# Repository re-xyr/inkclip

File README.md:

# Inkclip

Inkclip is an e-paper hair clip.

## Features

- It looks cool, if you are the type of person who thinks this kind of things look cool.
- Use it as more than a hair clip: a pin, a pocket clip, or just a gadget on your desktop.
- Update the pattern on the hair clip by simply connecting it to a computer via USB.
  - There is a ready-made web application you can use for this!
- Everything is open source: the hardware, the firmware, and the webapp.

## Physical characteristics

- Display size: 1.54 inches
- Resolution: 200 x 200 px
- Color: black and white
- Thickness (average): 2.60mm
- Thickness (thickest): 5.00mm (at micro-B port)
- Minimum weight (without mounting hardware): 6.5g
- Typical weight (with a 35mm hair clip): 8.0g
- Size: 33.40mm x 33.92mm
  - The shape of the device is a 32.80mm x 38.32mm rectangle with 1mm-radius dogbone corners.

## Project structure

- `hardware/` is the KiCad project for the Inkclip hardware.
- `firmware/` is a simple firmware for Inkclip that receives image bitmaps and then updates the entire display.
- `webapp/` is a web application for updating the display that works with the aforementioned firmware.

## Demo

## License

The hardware design portion of this project is available under the *CERN Open Hardware Licence Version 2 - Strongly Reciprocal (`CERN-OHL-S-2.0`)* while the software portion is available under the *GNU General Public License v3.0 or later (`GPL-3.0-or-later`)*. For details, refer to the `LICENSE` files under each subdirectory of this repository.

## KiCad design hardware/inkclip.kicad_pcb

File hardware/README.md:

# PCB design files of Inkclip

This is the [KiCad](https://www.kicad.org/) project for the PCB design of Inkclip. This PCB is designed to work with [Waveshare's 1.54-inch e-paper](https://www.waveshare.com/product/1.54inch-e-paper.htm).

The shape of the PCB is a 32.80 x 38.32mm rectangle with 1mm-radius dogbone corners. This ensures 0.5mm clearance from the PCB edge to the e-paper everywhere along the edges. Approximately in the middle of the PCB there is a 7.5mm wide horizontal component-free zone where you may attach mounting solutions of your choice (e.g. a hairclip, a pin, a pocket clip, velcro, tape, etc).

Specifically notice that the 24-pin FPC connector must be *top-contact* since the FPC cable of the display module is supposed to bend over so that the display may be mounted on the back side of the PCB. The positioning of this FPC connector is under the assumption that the PCB is 1.0mm thick, which is the thinnest [JLCPCB](https://jlcpcb.com) could print without the price going up. If you plan to print a thinner/thicker PCB then you might need to adjust the position of this connector accordingly.

This design uses an [STM32F411CEU6](https://www.st.com/en/microcontrollers-microprocessors/stm32f411ce.html) MCU. It has 512kB flash and 128kB RAM, which should be significantly more than what is needed by the firmware provided in this repository. On the bottom-right corner of the PCB there are pin holes for SWD debugging in the order [GND, SWCLK, SWDIO, 3V3]. The pushbutton on the PCB pulls BOOT0 up, which brings the MCU into DFU mode where you can write firmware over USB.

## License

The hardware design of Inkclip, namely all files under this directory, is provided under [CERN Open Hardware License Version 2 - Strongly Reciprocal (`CERN-OHL-S-2.0`)](LICENSE).

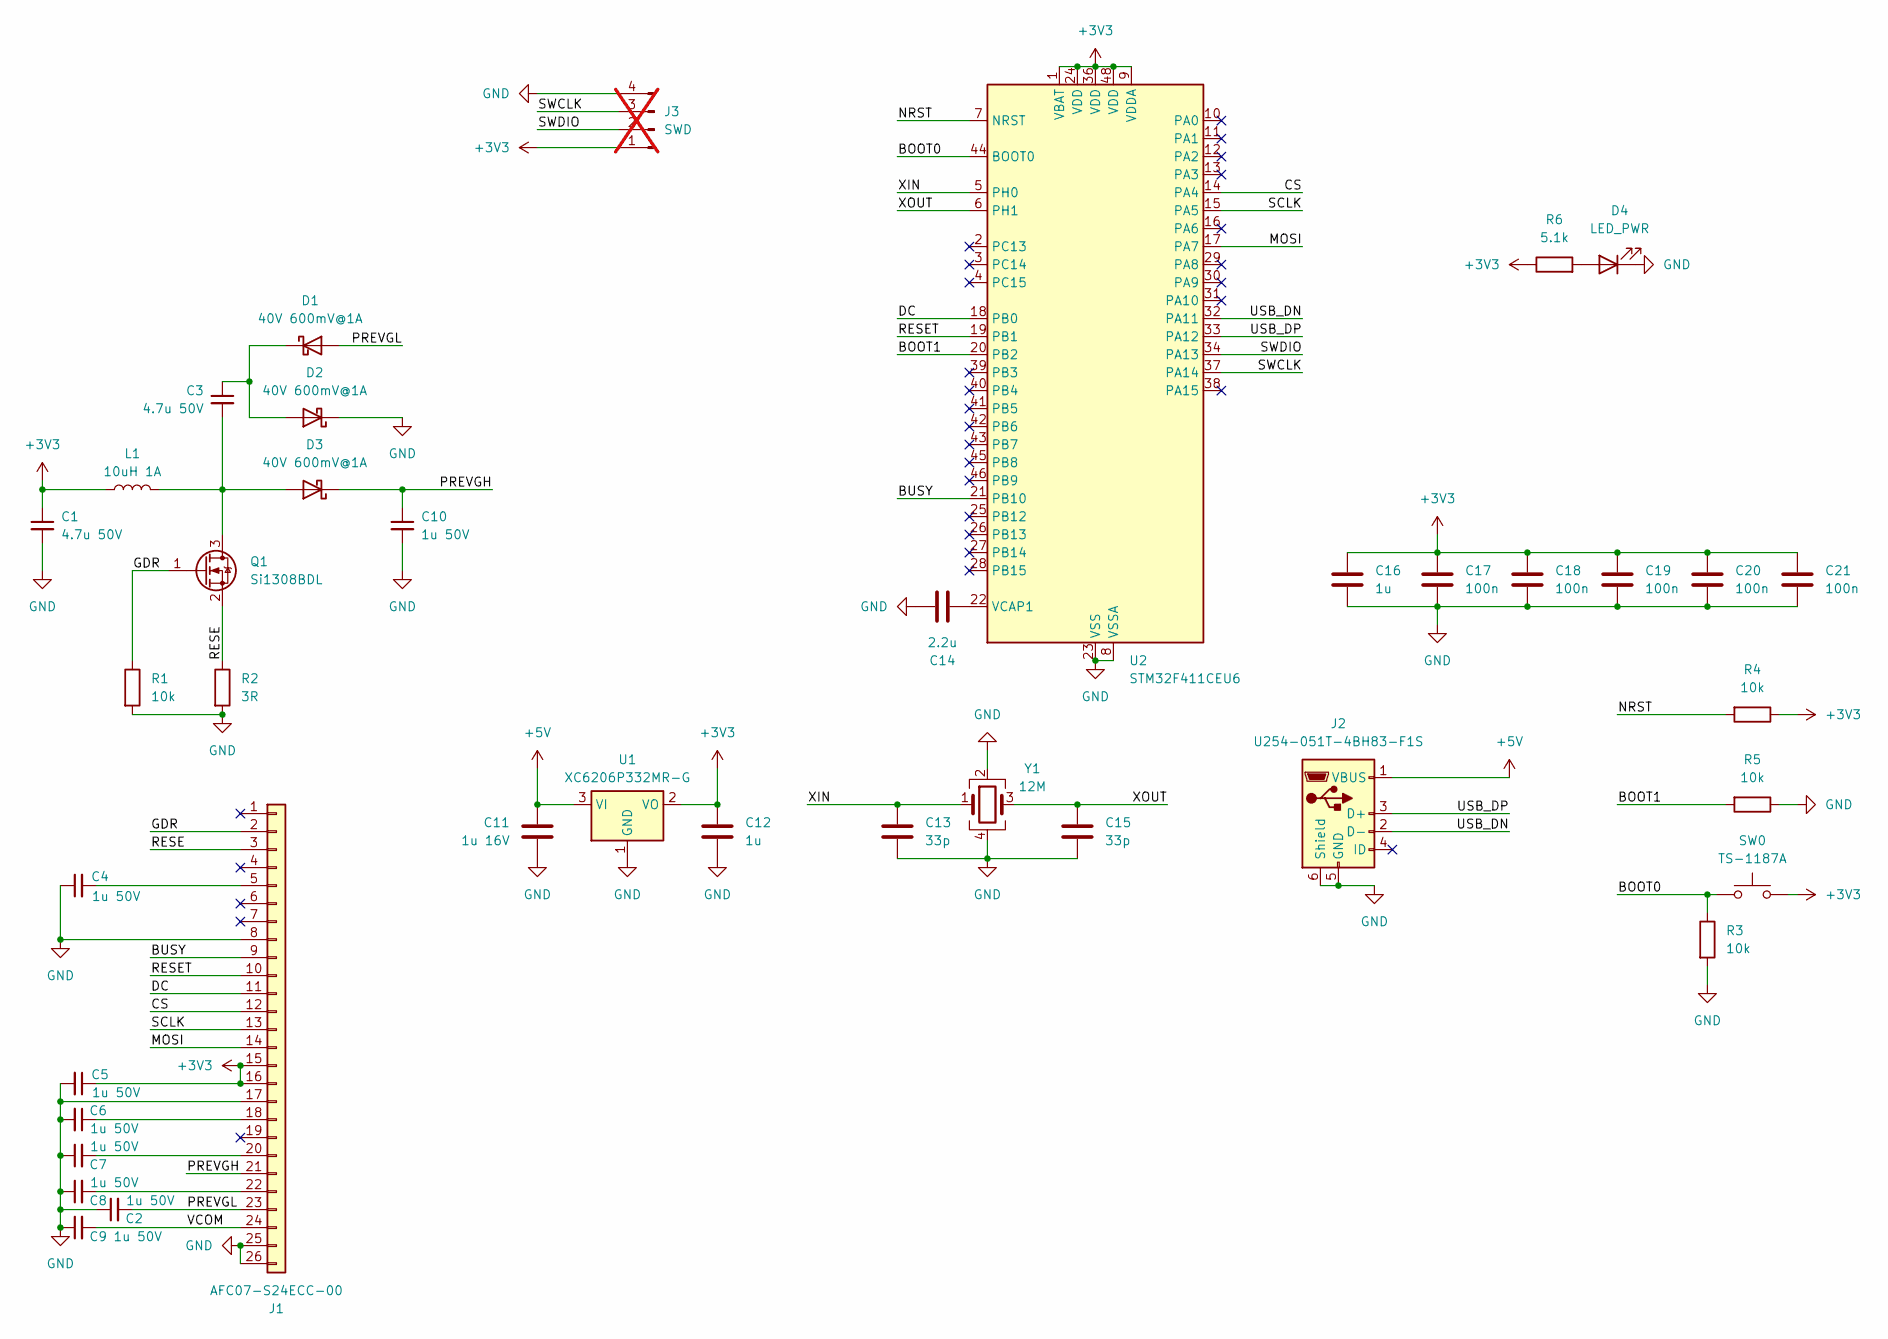
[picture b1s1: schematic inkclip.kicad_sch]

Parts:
C1, C3: 4.7u 50V; C_1206_3216Metric
C2, C4, C5, C6, C7, C8, C9, C10: 1u 50V; C_0603_1608Metric
C11: 1u 16V; C_0402_1005Metric
C12, C16: 1u; C_0402_1005Metric
C13, C15: 33p; C_0402_1005Metric
C14: 2.2u; C_0402_1005Metric
C17, C18, C19, C20, C21: 100n; C_0402_1005Metric
D1, D2, D3: 40V 600mV@1A; D_SOD-323
D4: LED_PWR; LED_0603_1608Metric
J1: AFC07-S24ECC-00; FPC-SMD_24P-L17.5-W5.4-P0.50
J2: U254-051T-4BH83-F1S; USB_Micro-B_XKB_U254-051T-4BH83-F1S
J3: SWD; PinHeader_1x04_P2.54mm_Vertical; not fitted
L1: 10uH 1A; L_Changjiang_FNR4018S
Q1: Si1308BDL; SOT-323_SC-70
R1, R3, R4, R5: 10k; R_0402_1005Metric
R2: 3R; R_0402_1005Metric
R6: 5.1k; R_0402_1005Metric
SW0: TS-1187A; SW_Push_1P1T_XKB_TS-1187A
U1: XC6206P332MR-G; SOT-23-3
U2: STM32F411CEU6; QFN-48-1EP_7x7mm_P0.5mm_EP5.6x5.6mm
Y1: 12M; Crystal_SMD_3225-4Pin_3.2x2.5mm

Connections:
+3V3: C1.1, C5.1, C12.1, C16.1, C17.1, C18.1, C19.1, C20.1, C21.1, J1.15, J1.16, J3.1, L1.1, R4.1, R6.1, SW0.2, U1.2 (VO), U2.1 (VBAT), U2.9 (VDDA), U2.24 (VDD), U2.36 (VDD), U2.48 (VDD)
+5V: C11.1, J2.1 (VBUS), U1.3 (VI)
/BOOT0: R3.1, SW0.1, U2.44 (BOOT0)
/BOOT1: R5.2, U2.20 (PB2)
/BUSY: J1.9, U2.21 (PB10)
/CS: J1.12, U2.14 (PA4)
/DC: J1.11, U2.18 (PB0)
/GDR: J1.2, Q1.1 (G), R1.1
/LED: U2.25 (PB12)
/MOSI: J1.14, U2.17 (PA7)
/NRST: R4.2, U2.7 (NRST)
/PREVGH: C10.1, D3.1 (K), J1.21
/PREVGL: C2.2, D1.2 (A), J1.23
/RESE: J1.3, Q1.2 (S), R2.1
/RESET: J1.10, U2.19 (PB1)
/SCLK: J1.13, U2.15 (PA5)
/SWCLK: J3.3, U2.37 (PA14)
/SWDIO: J3.2, U2.34 (PA13)
/USB_DN: J2.2 (D-), U2.32 (PA11)
/USB_DP: J2.3 (D+), U2.33 (PA12)
/VCOM: C9.2, J1.24
/XIN: C13.1, U2.5 (PH0), Y1.1
/XOUT: C15.1, U2.6 (PH1), Y1.3
GND: C1.2, C2.1, C4.1, C5.2, C6.2, C7.1, C8.1, C9.1, C10.2, C11.2, C12.2, C13.2, C14.1, C15.2, C16.2, C17.2, C18.2, C19.2, C20.2, C21.2, D2.1 (K), D4.1 (K), J1.8, J1.17, J1.25, J1.26, J2.5 (GND), J2.6 (Shield), J3.4, R1.2, R2.2, R3.2, R5.1, U1.1 (GND), U2.8 (VSSA), U2.23 (VSS), U2.35 (VSS), U2.47 (VSS), U2.49 (VSS), Y1.2, Y1.4
unnamed: C3.1, D1.1 (K), D2.2 (A)
unnamed: C3.2, D3.2 (A), L1.2, Q1.3 (D)
unnamed: D4.2 (A), R6.2
unnamed: C4.2, J1.5
unnamed: C6.1, J1.18
unnamed: C7.2, J1.20
unnamed: C8.2, J1.22
unnamed: C14.2, U2.22 (VCAP1)

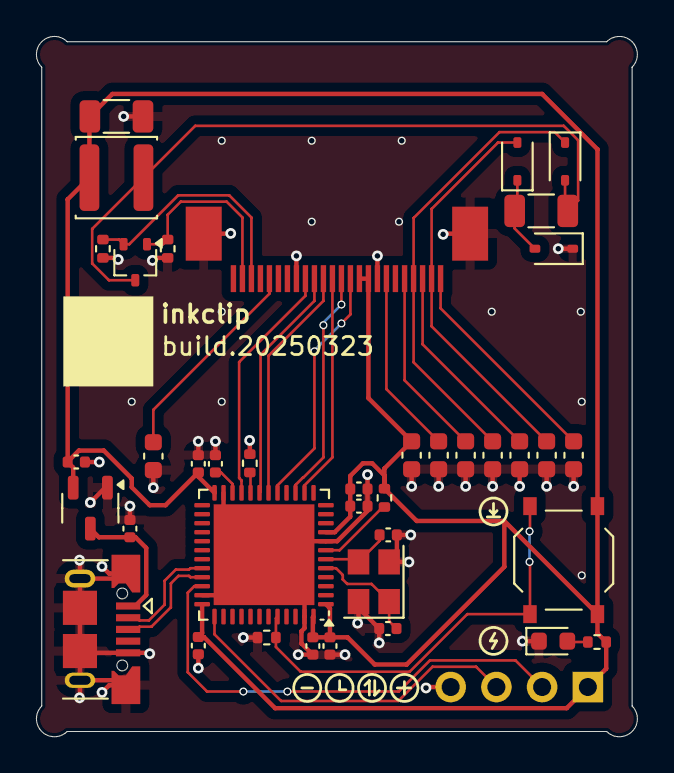
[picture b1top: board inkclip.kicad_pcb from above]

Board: 2 copper layers, 33.4 x 38.9 mm, 40 parts (1 on the bottom side), 31 nets.

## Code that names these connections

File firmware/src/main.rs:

#![no_main]
#![no_std]

use crate::{
    app::app_task,
    epd::Epd,
    midi::{make_midi_class, make_usb_builder, usb_task},
};

use defmt_rtt as _;
use embassy_executor::{Spawner, main};
use embassy_stm32::{
    Peripherals, bind_interrupts,
    peripherals::USB_OTG_FS,
    time::Hertz,
    usb::{self},
};
#[cfg(not(debug_assertions))]
use panic_abort as _;
#[cfg(debug_assertions)]
use panic_probe as _;

macro_rules! static_ref {
    ($ty:ty = $expr:expr) => {{
        static CELL: static_cell::StaticCell<$ty> = StaticCell::new();
        CELL.init($expr)
    }};
}

mod app;
mod epd;
mod midi;
mod pack;
mod sysex;
mod uid;

bind_interrupts!(pub struct Irqs {
  OTG_FS => usb::InterruptHandler<USB_OTG_FS>;
});

fn init_peripherals() -> Peripherals {
    embassy_stm32::init({
        use embassy_stm32::rcc::*;
        let mut config = embassy_stm32::Config::default();

        config.rcc.hse = Some(Hse {
            freq: Hertz(12_000_000),
            mode: HseMode::Oscillator,
        });
        config.rcc.pll_src = PllSource::HSE;
        config.rcc.pll = Some(Pll {
            prediv: PllPreDiv::DIV12,  // 12 / 12 = 1 MHz
            mul: PllMul::MUL192,       // 1 * 192 = 192 MHz
            divp: Some(PllPDiv::DIV2), // 192 / 2 = 96 MHz <= 100 MHz max freq
            divq: Some(PllQDiv::DIV4), // 192 / 4 = 48 MHz necessary for USB
            divr: None,
        });
        config.rcc.ahb_pre = AHBPrescaler::DIV1;
        config.rcc.apb1_pre = APBPrescaler::DIV2;
        config.rcc.apb2_pre = APBPrescaler::DIV4;
        config.rcc.sys = Sysclk::PLL1_P;
        config.rcc.mux.clk48sel = mux::Clk48sel::PLL1_Q;

        config
    })
}

#[main]
async fn main(spawner: Spawner) {
    let peri = init_peripherals();
    let epd = Epd::new(
        peri.SPI1, peri.PA4, peri.PA5, peri.PA7, peri.PB10, peri.PB0, peri.PB1,
    );

    let mut usb_builder = make_usb_builder(peri.USB_OTG_FS, peri.PA12, peri.PA11).await;
    let midi = make_midi_class(&mut usb_builder);

    spawner.must_spawn(usb_task(usb_builder));
    spawner.must_spawn(app_task(epd, midi));
}

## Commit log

2025-03-31 Rewrite using shadcn-svelte and tailwindcss
2025-03-31 Optimize dependencies
2025-03-31 Fix several bugs related to the interaction between reactivity and imperative browser APIs
2025-03-31 Improve typography
2025-03-31 Improve UI consistency
2025-03-31 Improve error reporting
2025-04-02 Refactor application
    - Use contexts for large-scope states
    - Use OffscreenCanvas for rendering instead of hidden canvas element
2025-04-03 Tweak the style of file input
2025-04-03 Pass aria-labelledby to the correct component in sliders
2025-04-03 Refactor codebase
    - Support file drag-and-drop
    - Fix wrong usage of tooltips
    - Add tailwind shorthands for layouting
    - Complete ARIA annotating
2025-04-03 Remove unused checkbox component
2025-04-03 Dynamically update the copyright year in the footer
2025-04-03 Improve accessibility
    - Sliders all have step=1 now
    - Indicate live regions for the two status text elements
2025-04-03 Multiple refactors
    - Use aria-labelledby instead of aria-label where possible
    - Replace magic numbers with explicitly defined constants
    - Add input textboxes for values previously only changed with sliders
2025-04-03 Add meta tags to <head>
2025-04-04 Improve accessibility
    - Add alt text for image preview
    - Add hidden <h1> heading
2025-04-04 Change default dithering kernel to Atkinson
2025-04-04 Rename constants
2025-04-04 Remove extraneous prop
2025-04-05 Change the cursor to a pointer when hovering over sliders
2025-04-05 Update dependencies
2025-04-05 Remove event listeners on dismount for reactive primitives
2025-04-05 Decouple imageIsCorrectRatio from ImageContext
2025-04-05 Add serial number display
2025-04-06 Tweak serial number communication
2025-04-07 Write an actual README
2025-04-07 Rename 'bias' to 'brightness', which is the more common terminology
2025-04-07 Move the webapp into a subdirectory
2025-04-07 webapp: turn off checkJs in tsconfig
2025-04-07 firmware: add firmware
2025-04-08 hardware: add hardware
2025-04-08 firmware: add README
2025-04-08 hardware: add README
2025-04-08 add building instructions
2025-04-08 Add a general README
2025-04-08 hardware: remove draft Edge.Cuts
2025-04-08 Add licenses
2025-09-07 Remove "Arc" from recommended list of Chromium-based browsers
    Reason: Arc seems to be on life support now.
2025-09-07 Remove incorrectly disallowed paths from robots.txt
2025-09-07 Migrate to Cloudflare Workers
2026-01-09 Rewrite firmware: use postcard over USB MIDI (SysEx)
2026-01-09 Crudely adapt webapp to new firmware
2026-01-09 Fix a panic when checking for magic number in firmware
2026-01-09 Move DeviceType to first position in GetIdentification
2026-01-10 Various build size optimizations
2026-01-10 Misc firmware improvements
2026-01-10 Add a ping method
2026-01-10 Reduce and calibrate RAM usage in firmware
2026-01-10 Fix a small calculation error for buffer size
2026-01-10 Implement more systematic logging in webapp
2026-01-12 Fix webapp mobile layout
2026-01-12 Fix screen rotation in firmware
2026-01-12 Bring packages and UI library up to date
2026-01-13 Implement MIDI permission detection and user prompting
2026-01-13 Fix minor alignment jank
2026-01-13 Remove mention of Firefox in the unsupported dialog
2026-01-14 Enforce consistent formatting in webapp source
2026-01-14 Slightly reword MIDI permission dialogs
2026-01-14 Add PWA support to webapp
2026-01-14 Reload page when new service worker is loaded
2026-01-14 Change theme-color based on color scheme
2026-01-14 Size ImplicitNumericInput more precisely on browsers that don't support field-sizing
2026-01-15 Use an actual logo
2026-01-15 Add a TWA
2026-01-15 Make write section sticky
2026-01-15 Move around breakpoints in connect/write sections
2026-01-16 Update icon
2026-01-16 Update TWA
2026-01-16 Use system UI font for webapp
2026-01-16 Try to persist data when installed as a PWA
2026-01-16 Prevent UI resizing from pinch and virtual keyboard
2026-01-16 Add some flow guidance in the form of title opacity/weight changes
